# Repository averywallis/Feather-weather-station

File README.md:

# Feather-weather-station
 KiCad files for a Weather Station Featherwing

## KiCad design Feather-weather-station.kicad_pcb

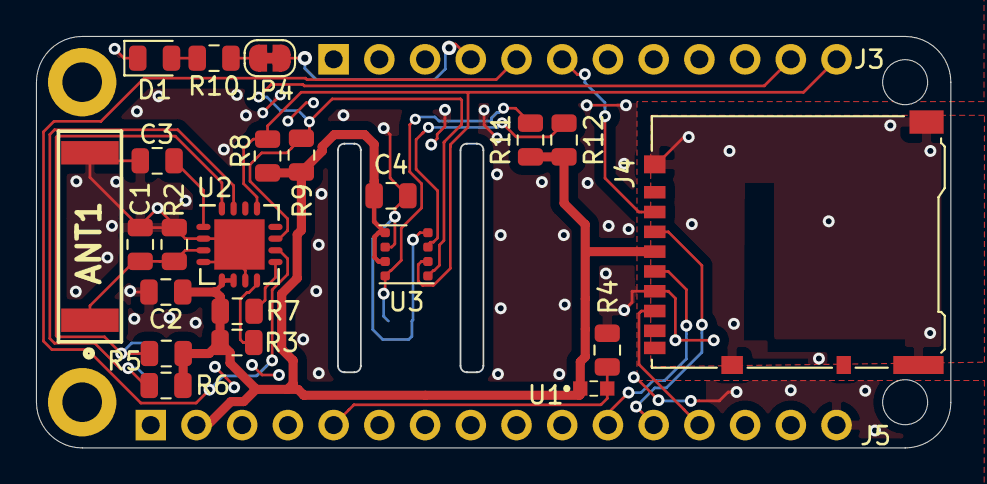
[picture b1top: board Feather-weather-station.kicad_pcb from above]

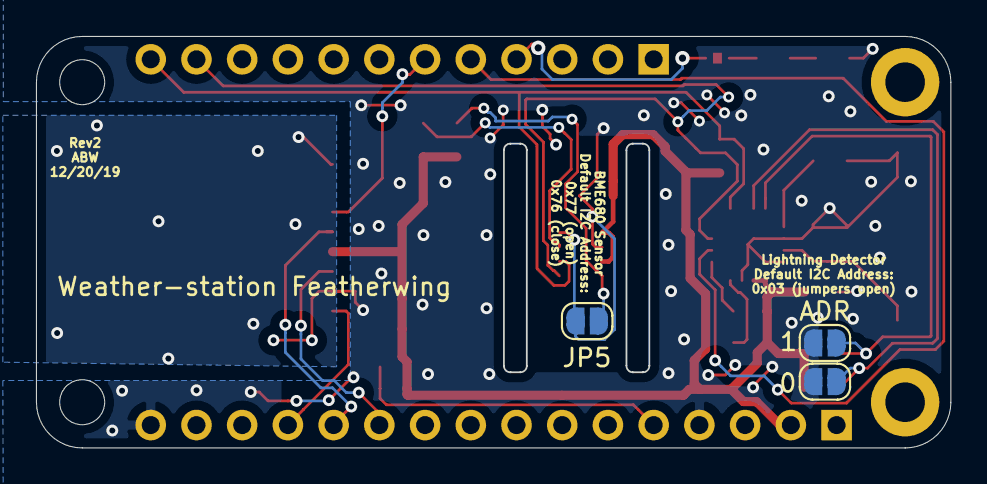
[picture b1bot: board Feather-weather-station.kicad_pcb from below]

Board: 2 copper layers, 50.8 x 22.8 mm, 27 parts (3 on the bottom side), 21 nets.

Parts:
ANT1: MA5532-AEB; MA5532
C1: 1nF; C_0805_2012Metric
C2, C4: 1.0uF; C_0805_2012Metric
C3: 10uF; C_0805_2012Metric
D1: LED; LED_0805_2012Metric
J3: Conn_01x12; PinHeader_1x12_P2.54mm_Vertical
J4: Micro_SD_Card_Det; microSD_HC_Hirose_DM3AT-SF-PEJM5
J5: Conn_01x16; PinHeader_1x16_P2.54mm_Vertical
JP2, JP3, JP5: SolderJumper-2_P1.3mm_Open_RoundedPad1.0x1.5mm
JP4: SolderJumper_2_Bridged; SolderJumper-2_P1.3mm_Bridged_RoundedPad1.0x1.5mm
R2, R3, R4, R5, R6, R7, R8, R9, R11, R12: 10k; R_0805_2012Metric
R10: 1k; R_0805_2012Metric
U1: ALSPT19315CL177TR8
U2: AS3935; MLPQ-16-1EP_4x4mm_P0.65mm_EP2.8x2.8mm
U3: BME680; Bosch_LGA-8_3x3mm_P0.8mm_ClockwisePinNumbering

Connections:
+3V3: C2.1, C4.1, J4.4, J5.2, R3.1, R5.1, R6.1, R7.2, R8.1, R9.1, R11.1, R12.2, U1.1, U2.5, U2.6, U3.6, U3.8
/11`: J3.6, J4.2
/12: J3.5, U2.10
/13: J3.4, JP4.1
/A0: J5.5, R4.1, U1.2
/AD0: JP2.1, R6.2, U2.15
/AD1: JP3.1, R5.2, U2.16
/Antenna: ANT1.1, C1.1, R2.1, U2.3
/MISO: J4.7, J5.13
/MOSI: J4.3, J5.12
/SCK: J4.5, J5.11
/SCL: J3.11, R9.2, U2.11, U3.4
/SDA: J3.12, R8.2, U2.13, U3.3
/SELECT_INTERFACE: R7.1, U2.9
GND: ANT1.2, C1.2, C2.2, C3.2, C4.2, D1.1, J4.6, J5.4, J5.16, JP2.2, JP3.2, JP5.1, R2.2, R4.2, U2.2, U2.4, U2.7, U2.17, U3.1, U3.7
unnamed: C3.1, U2.1
unnamed: D1.2, R10.2
unnamed: JP4.2, R10.1
unnamed: JP5.2, R11.2, U3.5
unnamed: R3.2, U2.8
unnamed: R12.1, U3.2

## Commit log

2022-01-29 Create LICENSE
